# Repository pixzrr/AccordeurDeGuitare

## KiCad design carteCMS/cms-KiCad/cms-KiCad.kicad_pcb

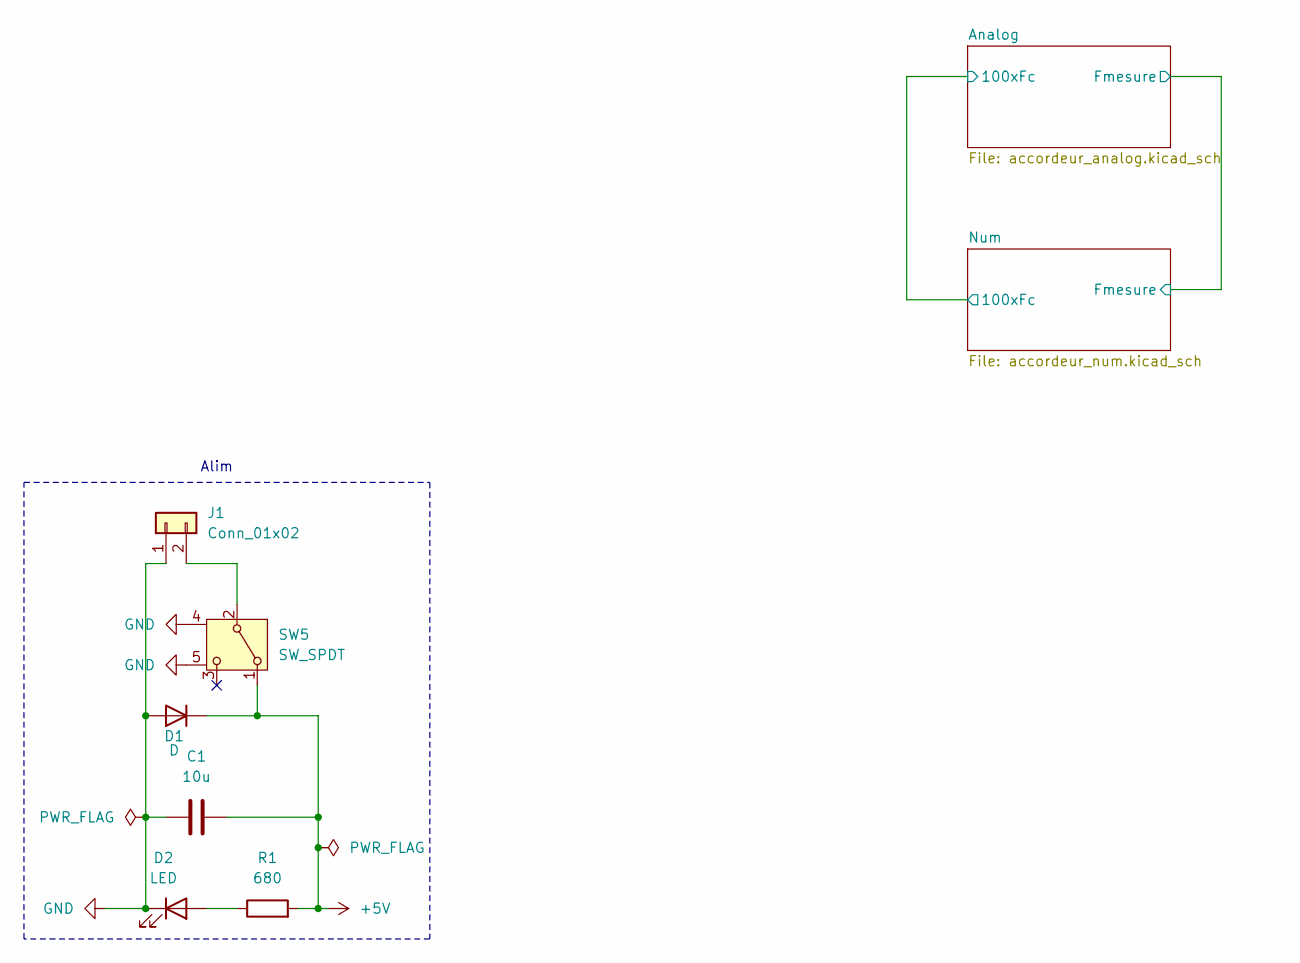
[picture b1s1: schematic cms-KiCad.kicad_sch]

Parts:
C1: 10u; C_0805_2012Metric
D1: D; D_0805_2012Metric
D2: LED; LED_0805_2012Metric
J1: Conn_01x02; conn01x02Alim-CTB52022
R1: 680; R_0805_2012Metric
SW5: SW_SPDT; SWITCH_11MA1QS1

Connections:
+5V: C1.2, D1.1 (K), R1.2, SW5.1 (A); also elsewhere on the board
GND: C1.1, D1.2 (A), D2.1 (K), J1.1, SW5.4 (carcasse1), SW5.5 (carcasse2); also elsewhere on the board
unnamed: D2.2 (A), R1.1
unnamed: J1.2, SW5.2 (B)

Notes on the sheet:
Alim

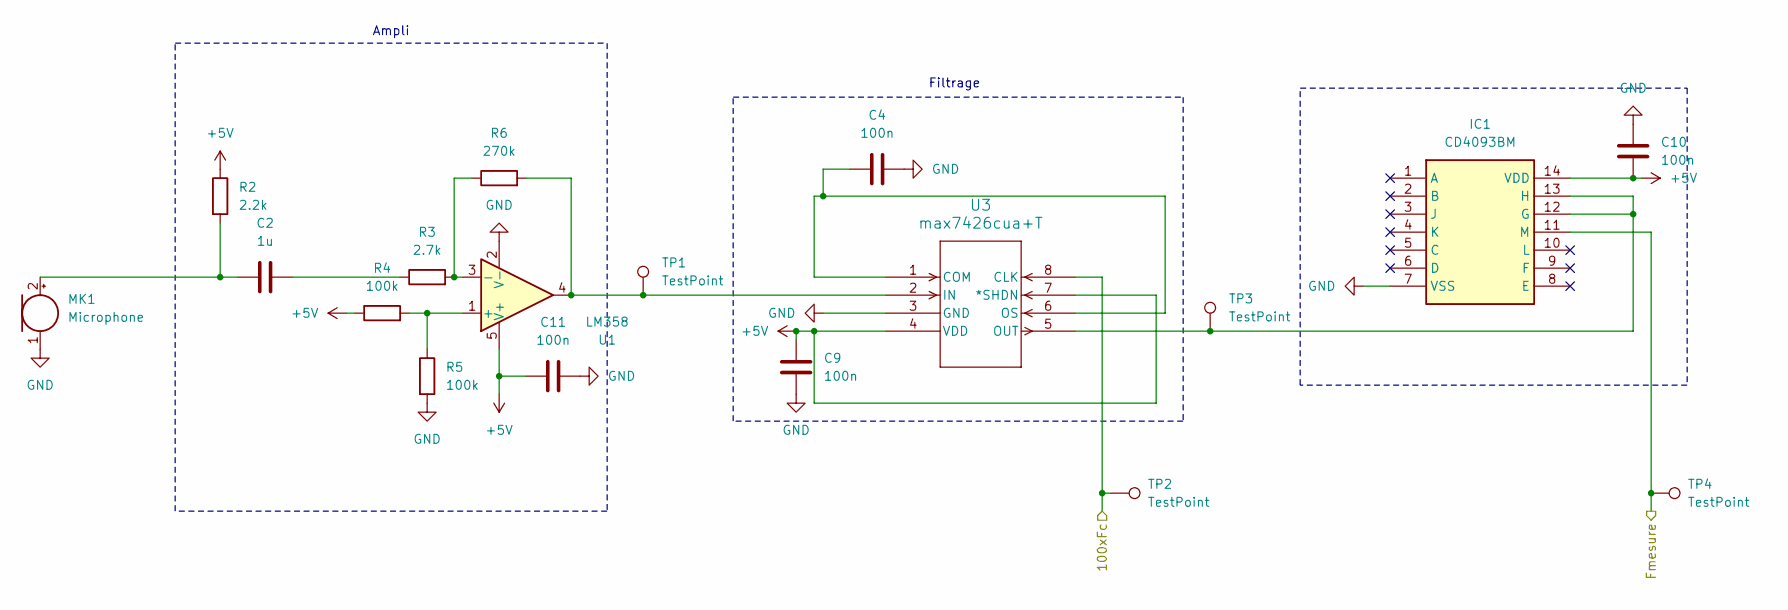
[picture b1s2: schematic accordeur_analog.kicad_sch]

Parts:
C2: 1u; C_0805_2012Metric
C4, C9, C10, C11: 100n; C_0805_2012Metric
IC1: CD4093BM; SO-14_5.3x10.2mm_P1.27mm; Mouser Part Number 595-CD4093BM
MK1: Microphone; micro-KECG2740PBJ
R2: 2.2k; R_0805_2012Metric
R3: 2.7k; R_0805_2012Metric
R4, R5: 100k; R_0805_2012Metric
R6: 270k; R_0805_2012Metric
TP1, TP2, TP3, TP4: TestPoint; TestPoint_Pad_D2.0mm
U1: LM358; SOT-353_SC-70-5
U3: max7426cua+T; MAX7426

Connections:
+5V: C9.1, C10.2, C11.1, IC1.14 (VDD), R2.1, R4.1, U1.5 (V+), U3.4 (VDD), U3.7 (*SHDN); also elsewhere on the board
/Analog/100xFc: TP2.1, U3.8 (CLK); also elsewhere on the board
/Analog/Fmesure: IC1.11 (M), TP4.1; also elsewhere on the board
GND: C4.1, C9.2, C10.1, C11.2, IC1.7 (VSS), MK1.1 (-), R5.2, U1.2 (V-), U3.3 (GND); also elsewhere on the board
unnamed: C2.2, R3.1
unnamed: IC1.12 (G), IC1.13 (H), TP3.1, U3.5 (OUT)
unnamed: C2.1, MK1.2 (+), R2.2
unnamed: R4.2, R5.1, U1.1 (+)
unnamed: R3.2, R6.1, U1.3 (-)
unnamed: C4.2, U3.1 (COM), U3.6 (OS)
unnamed: R6.2, TP1.1, U1.4, U3.2 (IN)

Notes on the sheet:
Ampli
Filtrage

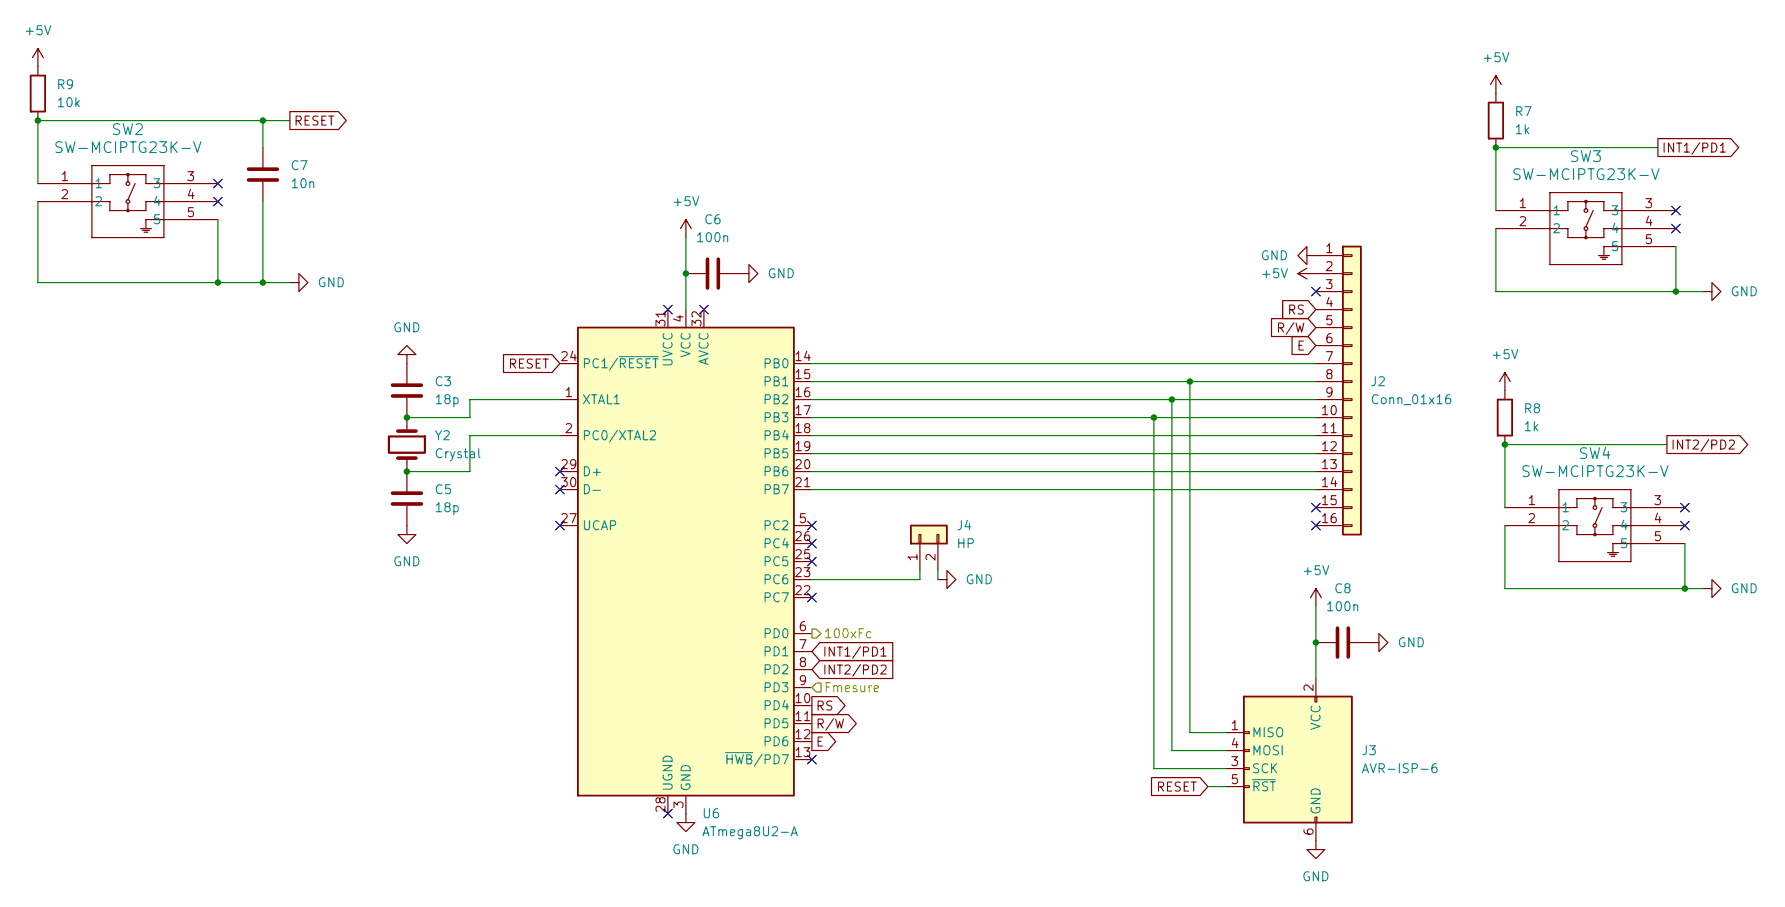
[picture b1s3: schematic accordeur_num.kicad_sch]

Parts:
C3, C5: 18p; C_0805_2012Metric
C6, C8: 100n; C_0805_2012Metric
C7: 10n; C_0805_2012Metric
J2: Conn_01x16; PinSocket_1x16_P2.54mm_Vertical
J3: AVR-ISP-6; PinHeader_2x03_P2.54mm_Vertical
J4: HP; PinHeader_1x02_P2.54mm_Vertical
R7, R8: 1k; R_0805_2012Metric
R9: 10k; R_0805_2012Metric
SW2, SW3, SW4: SW-MCIPTG23K-V; SW-MCIPTG23K-V_MTC
U6: ATmega8U2-A; TQFP-32_7x7mm_P0.8mm
Y2: Crystal; quartz-HC49USMFB5F2016000MHZ

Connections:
+5V: C6.1, C8.1, J2.2, J3.2 (VCC), R7.1, R8.1, R9.1, U6.4 (VCC); also elsewhere on the board
/Analog/100xFc: U6.6 (PD0); also elsewhere on the board
/Analog/Fmesure: U6.9 (PD3); also elsewhere on the board
E: J2.6, U6.12 (PD6)
GND: C3.1, C5.2, C6.2, C7.2, C8.2, J2.1, J3.6 (GND), J4.2, SW2.2, SW2.5, SW3.2, SW3.5, SW4.2, SW4.5, U6.3 (GND); also elsewhere on the board
INT1/PD1: R7.2, SW3.1, U6.7 (PD1)
INT2/PD2: R8.2, SW4.1, U6.8 (PD2)
unnamed: J2.7, U6.14 (PB0)
unnamed: J2.8, J3.1 (MISO), U6.15 (PB1)
unnamed: J2.9, J3.4 (MOSI), U6.16 (PB2)
unnamed: J2.10, J3.3 (SCK), U6.17 (PB3)
unnamed: J2.11, U6.18 (PB4)
unnamed: J2.12, U6.19 (PB5)
unnamed: J2.13, U6.20 (PB6)
unnamed: J2.14, U6.21 (PB7)
unnamed: J4.1, U6.23 (PC6)
unnamed: C5.1, U6.2 (PC0/XTAL2), Y2.2
unnamed: C3.2, U6.1 (XTAL1), Y2.1
RESET: C7.1, J3.5 (~RST), R9.2, SW2.1, U6.24 (PC1/~RESET)
RS: J2.4, U6.10 (PD4)
R/W: J2.5, U6.11 (PD5)

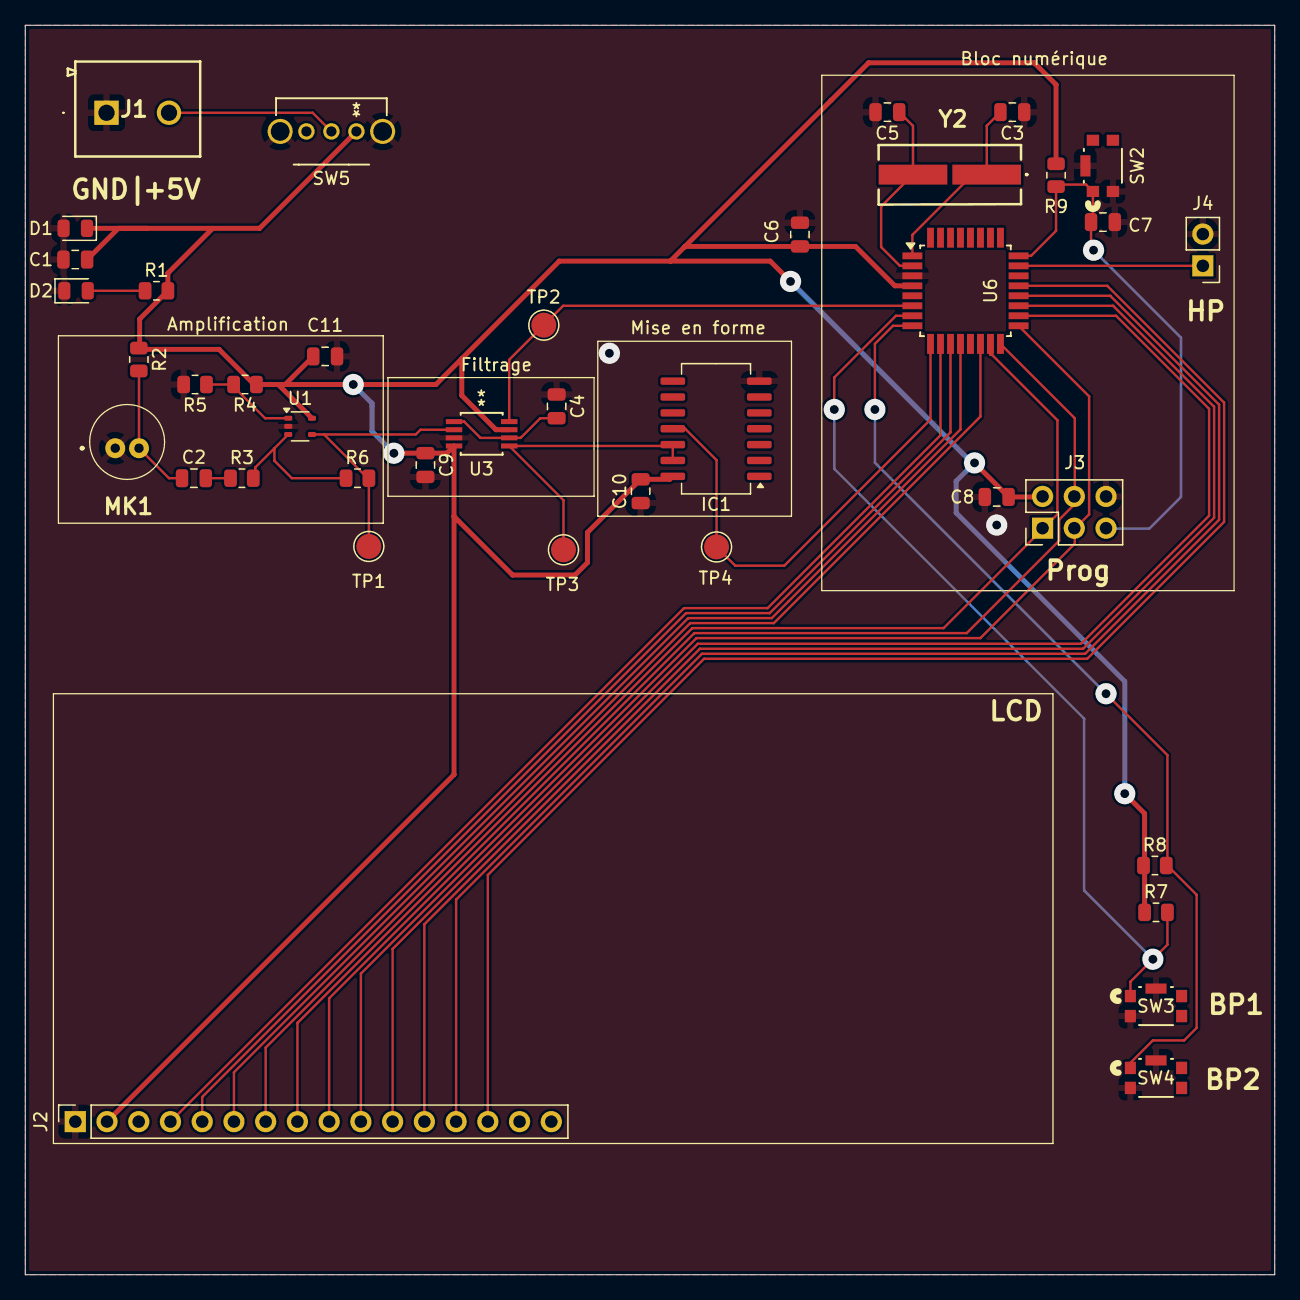
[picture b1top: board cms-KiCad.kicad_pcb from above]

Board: 2 copper layers, 100.0 x 100.0 mm, 40 parts (0 on the bottom side), 30 nets.
